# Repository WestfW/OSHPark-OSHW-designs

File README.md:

# OSHPark-OSHW-designs
I have some PCB projects that I've made public on OSHPark.  This is where I'll put the "source code" and any documentation that may exist.

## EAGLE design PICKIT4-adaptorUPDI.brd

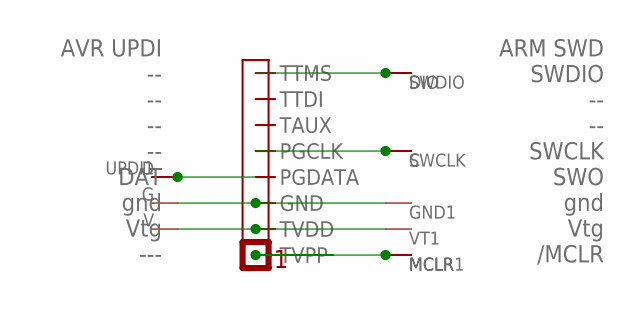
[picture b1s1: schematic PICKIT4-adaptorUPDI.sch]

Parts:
C: WIRER; GENERIC-RD-1
D: WIRER; GENERIC-RD-1
DIO: WIRER; GENERIC-RD-1
G: WIRER; GENERIC-RD-1
GND1: WIRE-R12; VIA12
MCLR: WIRE-R12; VIA12
MCLR1: WIRER; GENERIC-RD-1
SWCLK: WIRE-R12; VIA12
SWDIO: WIRE-R12; VIA12
U$1: PICKIT4PINHDR; PINHEAD1X8
UPDI1: WIRE-R12; VIA12
V: WIRER; GENERIC-RD-1
VT1: WIRE-R12; VIA12

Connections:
GND: G.P$1, GND1.P$1, U$1.P$3 (GND)
unnamed: U$1.P$2 (TVDD), V.P$1, VT1.P$1
unnamed: D.P$1, U$1.P$4 (PGDATA), UPDI1.P$1
unnamed: C.P$1, SWCLK.P$1, U$1.P$5 (PGCLK)
TTMS: DIO.P$1, SWDIO.P$1, U$1.P$8 (TTMS)
TVPP: MCLR.P$1, MCLR1.P$1, U$1.P$1 (TVPP)

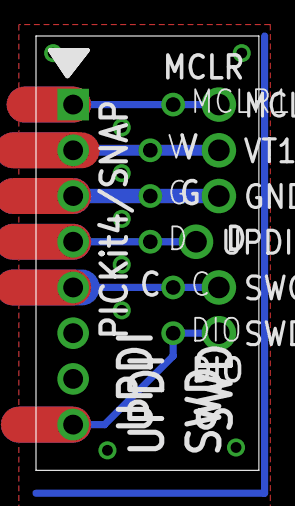
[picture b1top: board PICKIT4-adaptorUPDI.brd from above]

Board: 2 copper layers, 12.4 x 24.1 mm, 13 parts (0 on the bottom side), 6 nets.

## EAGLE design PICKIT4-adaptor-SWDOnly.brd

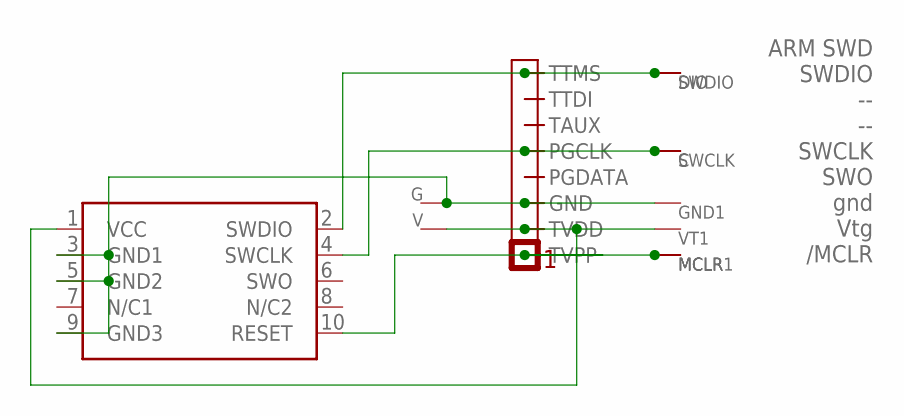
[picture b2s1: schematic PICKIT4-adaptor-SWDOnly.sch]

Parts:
C: WIRE-R12; VIA12
DIO: WIRE-R12; VIA12
G: WIRE-R12; VIA12
GND1: WIRE-R12; VIA12
MCLR, MCLR1: WIRE-R12; VIA12
SWCLK: WIRE-R12; VIA12
SWD1: CORTEX_SWD; M50-3600542
SWDIO: WIRE-R12; VIA12
U$1: PICKIT4PINHDR; PINHEAD1X8
V: WIRE-R12; VIA12
VT1: WIRE-R12; VIA12

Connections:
GND: G.P$1, GND1.P$1, SWD1.3 (GND1), SWD1.5 (GND2), SWD1.9 (GND3), U$1.P$3 (GND)
unnamed: SWD1.1 (VCC), U$1.P$2 (TVDD), V.P$1, VT1.P$1
unnamed: C.P$1, SWCLK.P$1, SWD1.4 (SWCLK), U$1.P$5 (PGCLK)
unnamed: MCLR.P$1, MCLR1.P$1, SWD1.10 (RESET), U$1.P$1 (TVPP)
TTMS: DIO.P$1, SWD1.2 (SWDIO), SWDIO.P$1, U$1.P$8 (TTMS)

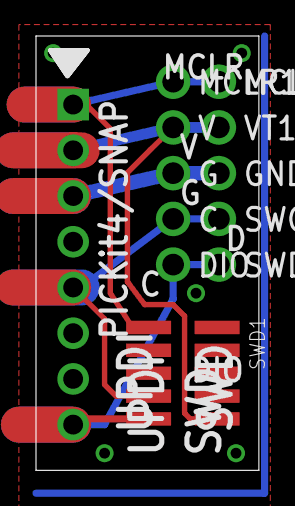
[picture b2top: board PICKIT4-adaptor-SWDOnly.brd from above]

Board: 2 copper layers, 12.4 x 24.1 mm, 12 parts (0 on the bottom side), 5 nets.

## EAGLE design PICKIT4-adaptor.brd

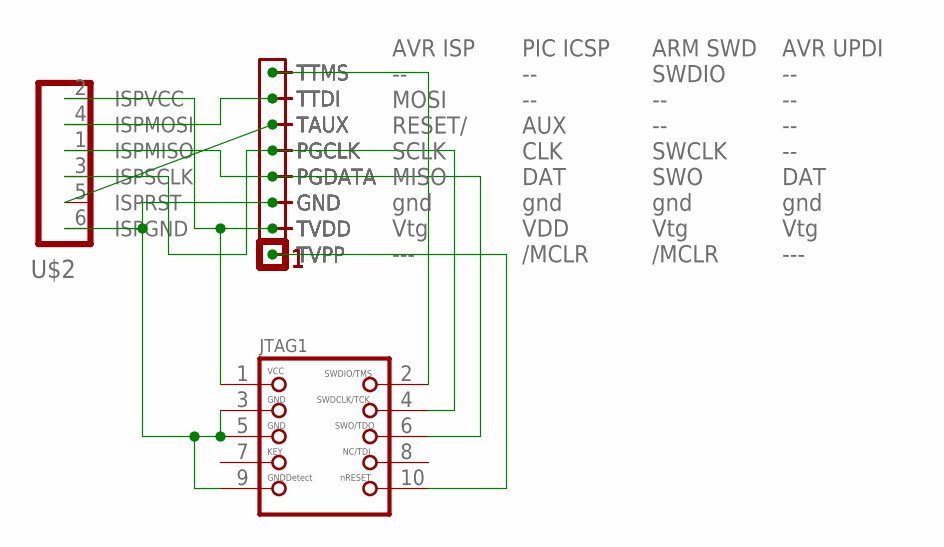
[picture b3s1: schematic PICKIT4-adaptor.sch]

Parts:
JTAG1: JTAG-CORTEXM3; 2X05_1.27MM_SMT
U$1, U$3, U$4: PICKIT4PINHDR; PINHEAD1X8
U$2: AVR-ISP; 6PINS

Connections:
CLK: JTAG1.4, U$1.P$5 (PGCLK), U$2.3 (ISPSCLK), U$3.P$5 (PGCLK), U$4.P$5 (PGCLK)
DATA: JTAG1.6, U$1.P$4 (PGDATA), U$2.1 (ISPMISO), U$3.P$4 (PGDATA), U$4.P$4 (PGDATA)
GND: JTAG1.3, JTAG1.5, JTAG1.9, U$1.P$3 (GND), U$2.6 (ISPGND), U$3.P$3 (GND), U$4.P$3 (GND)
TAUX: U$1.P$6 (TAUX), U$2.5 (ISPRST), U$3.P$6 (TAUX), U$4.P$6 (TAUX)
TTDI: U$1.P$7 (TTDI), U$2.4 (ISPMOSI), U$3.P$7 (TTDI), U$4.P$7 (TTDI)
TTMS: JTAG1.2, U$1.P$8 (TTMS), U$3.P$8 (TTMS), U$4.P$8 (TTMS)
TVDD: JTAG1.1, U$1.P$2 (TVDD), U$2.2 (ISPVCC), U$3.P$2 (TVDD), U$4.P$2 (TVDD)
VPP: JTAG1.10, U$1.P$1 (TVPP), U$3.P$1 (TVPP), U$4.P$1 (TVPP)

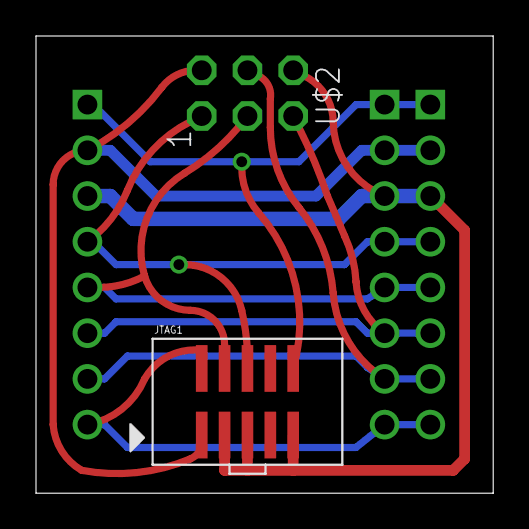
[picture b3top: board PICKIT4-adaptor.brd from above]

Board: 2 copper layers, 25.4 x 25.4 mm, 5 parts (0 on the bottom side), 8 nets.

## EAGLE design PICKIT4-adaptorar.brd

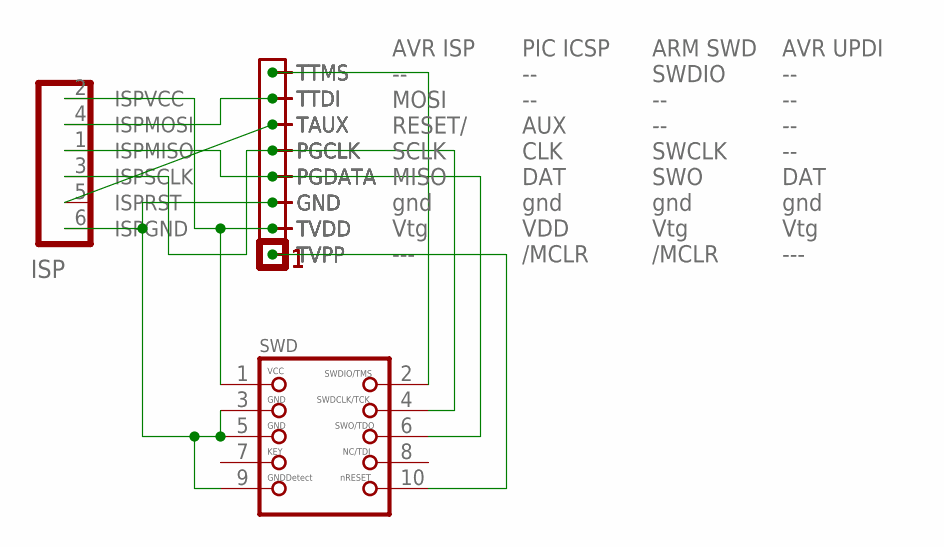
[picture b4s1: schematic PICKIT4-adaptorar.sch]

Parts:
ISP: AVR-ISP; 6PINS
SWD: JTAG-CORTEXM3; 2X05_1.27MM_SMT
U$1, U$3, U$4: PICKIT4PINHDR; PINHEAD1X8

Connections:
CLK: ISP.3 (ISPSCLK), SWD.4, U$1.P$5 (PGCLK), U$3.P$5 (PGCLK), U$4.P$5 (PGCLK)
DATA: ISP.1 (ISPMISO), SWD.6, U$1.P$4 (PGDATA), U$3.P$4 (PGDATA), U$4.P$4 (PGDATA)
GND: ISP.6 (ISPGND), SWD.3, SWD.5, SWD.9, U$1.P$3 (GND), U$3.P$3 (GND), U$4.P$3 (GND)
TAUX: ISP.5 (ISPRST), U$1.P$6 (TAUX), U$3.P$6 (TAUX), U$4.P$6 (TAUX)
TTDI: ISP.4 (ISPMOSI), U$1.P$7 (TTDI), U$3.P$7 (TTDI), U$4.P$7 (TTDI)
TTMS: SWD.2, U$1.P$8 (TTMS), U$3.P$8 (TTMS), U$4.P$8 (TTMS)
TVDD: ISP.2 (ISPVCC), SWD.1, U$1.P$2 (TVDD), U$3.P$2 (TVDD), U$4.P$2 (TVDD)
VPP: SWD.10, U$1.P$1 (TVPP), U$3.P$1 (TVPP), U$4.P$1 (TVPP)

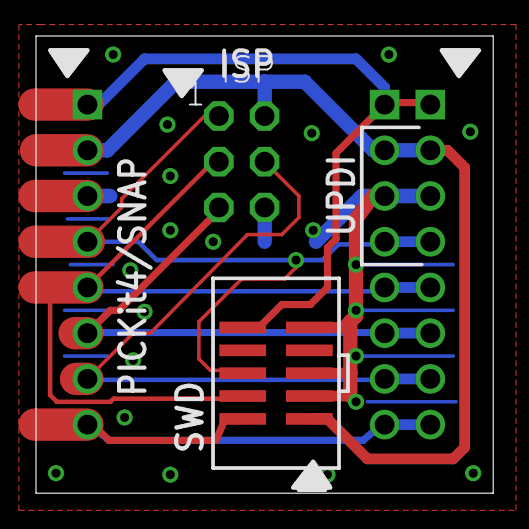
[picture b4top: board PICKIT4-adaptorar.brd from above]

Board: 2 copper layers, 25.4 x 25.4 mm, 5 parts (0 on the bottom side), 8 nets.

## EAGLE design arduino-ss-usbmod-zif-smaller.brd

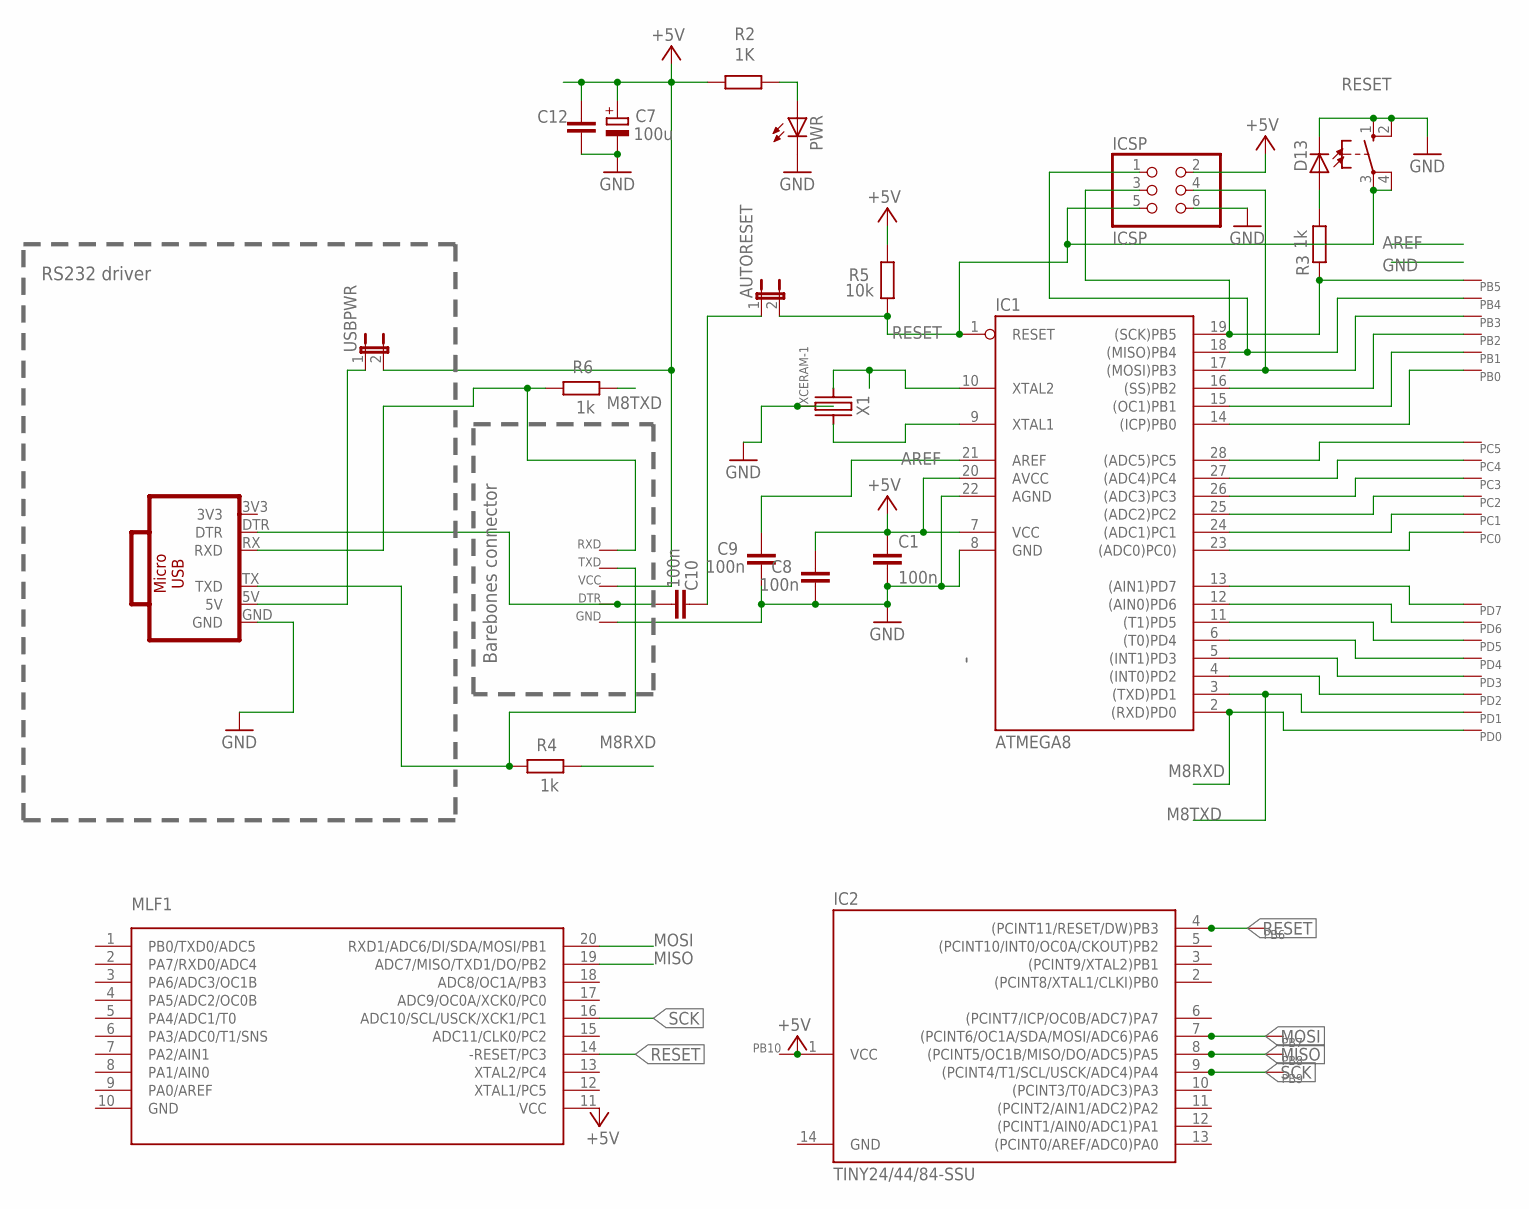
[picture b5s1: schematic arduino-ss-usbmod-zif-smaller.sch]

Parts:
AUTORESET: JUMPER-2PTH; 1X02
C1, C8, C9, C10, C12: 100n; C050-025X075
C7: 100u; E3,5-8
D13: LED3MM
DTR: WIRER; GENERIC-RD-1
GND: WIRER; GENERIC-RD-1
IC1: ATMEGA8; ZIF28/3
IC2: TINY24/44/84-SSU; SOIC14
ICSP: ICSP; 2X03
MLF1: ATTINY1634SOIC20; SOIC20
MOD1: CH340E-MODNOHOLES; CH340E-MOD-NOHOLES
PB0, PB1, PB2, PB3, PB4, PB5, PB6, PB7, PB8, PB9, PB10: WIRE-VIA11; VIA11
PC0: WIRER; GENERIC-RD-1
PC1, PC2, PC3, PC4, PC5: WIRE-VIA11; VIA11
PD0, PD1, PD2, PD3, PD4, PD5, PD6, PD7: WIRE-VIA11; VIA11
PWR: LED3MM
R2: 1K; 0207/7
R3: 1k; 0204/5
R4, R6: 1k; 0207/7
R5: 10k; 0207/7
RESET: 10-XX; B3F-10XX
RXD: WIRER; GENERIC-RD-1
TXD: WIRER; GENERIC-RD-1
USBPWR: JUMPER-2PTH; 1X02
VCC: WIRE-VIA11; VIA11
X1: XCERAM-1; XTAL-3

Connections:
3V3: MOD1.3V3
+5V: C1.1, C7.+, C8.2, C12.2, IC1.7 (VCC), IC1.20 (AVCC), IC2.1 (VCC), ICSP.2, MLF1.11 (VCC), PB10.P$1, R2.2, R5.2, USBPWR.2, VCC.P$1
AREF: C9.2, IC1.21 (AREF)
DTR: C10.1, DTR.P$1, MOD1.DTR
GND: C1.2, C7.-, C8.1, C9.1, C12.1, D13.K (C), GND.P$1, IC1.8 (GND), IC1.22 (AGND), IC2.14 (GND), ICSP.6, MLF1.10 (GND), MOD1.GND, PWR.K (C), RESET.1 (S), RESET.2 (S1), X1.P$2 (GND)
M8RXD: IC1.2 ((RXD)PD0), PD0.P$1, R4.1
M8TXD: IC1.3 ((TXD)PD1), PD1.P$1, R6.1
MISO: IC1.18 ((MISO)PB4), IC2.8 ((PCINT5/OC1B/MISO/DO/ADC5)PA5), ICSP.1, MLF1.19 (ADC7/MISO/TXD1/DO/PB2), PB4.P$1, PB8.P$1
MOSI: IC1.17 ((MOSI)PB3), IC2.7 ((PCINT6/OC1A/SDA/MOSI/ADC6)PA6), ICSP.4, MLF1.20 (RXD1/ADC6/DI/SDA/MOSI/PB1), PB3.P$1, PB7.P$1
unnamed: D13.A, R3.1
unnamed: MOD1.5V, USBPWR.1
unnamed: PWR.A, R2.1
unnamed: AUTORESET.1, C10.2
unnamed: IC1.14 ((ICP)PB0), PB0.P$1
unnamed: IC1.9 (XTAL1), X1.P$3
unnamed: IC1.10 (XTAL2), X1.P$1
unnamed: IC1.4 ((INT0)PD2), PD2.P$1
unnamed: IC1.5 ((INT1)PD3), PD3.P$1
unnamed: IC1.6 ((T0)PD4), PD4.P$1
unnamed: IC1.11 ((T1)PD5), PD5.P$1
unnamed: IC1.12 ((AIN0)PD6), PD6.P$1
unnamed: IC1.13 ((AIN1)PD7), PD7.P$1
unnamed: IC1.23 ((ADC0)PC0)), PC0.P$1
unnamed: IC1.24 ((ADC1)PC1), PC1.P$1
unnamed: IC1.25 ((ADC2)PC2), PC2.P$1
unnamed: IC1.26 ((ADC3)PC3), PC3.P$1
unnamed: IC1.27 ((ADC4)PC4), PC4.P$1
unnamed: IC1.28 ((ADC5)PC5), PC5.P$1
unnamed: IC1.15 ((OC1)PB1), PB1.P$1
unnamed: MOD1.TX (TXD), R4.2, TXD.P$1
unnamed: MOD1.RX (RXD), R6.2, RXD.P$1
RESET: AUTORESET.2, IC1.1 (RESET), IC2.4 ((PCINT11/RESET/DW)PB3), ICSP.5, MLF1.14 (-RESET/PC3), PB6.P$1, R5.1, RESET.3, RESET.4 (P1)
SCK: IC1.19 ((SCK)PB5), IC2.9 ((PCINT4/T1/SCL/USCK/ADC4)PA4), ICSP.3, MLF1.16 (ADC10/SCL/USCK/XCK1/PC1), PB5.P$1, PB9.P$1, R3.2
SS: IC1.16 ((SS)PB2), PB2.P$1

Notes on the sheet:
RS232 driver
Barebones connector

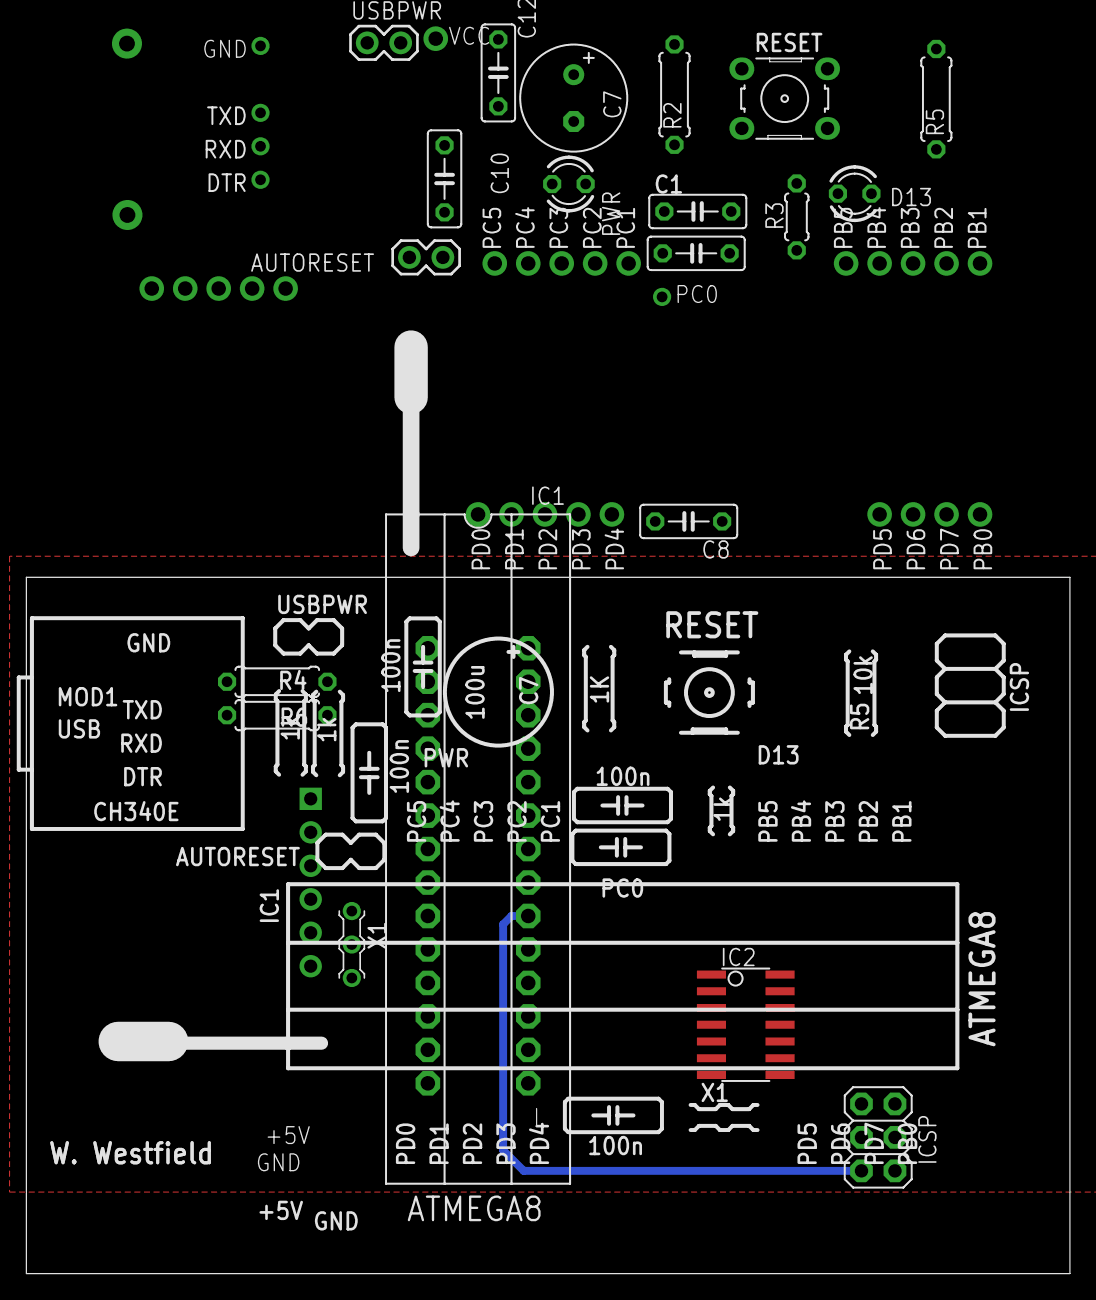
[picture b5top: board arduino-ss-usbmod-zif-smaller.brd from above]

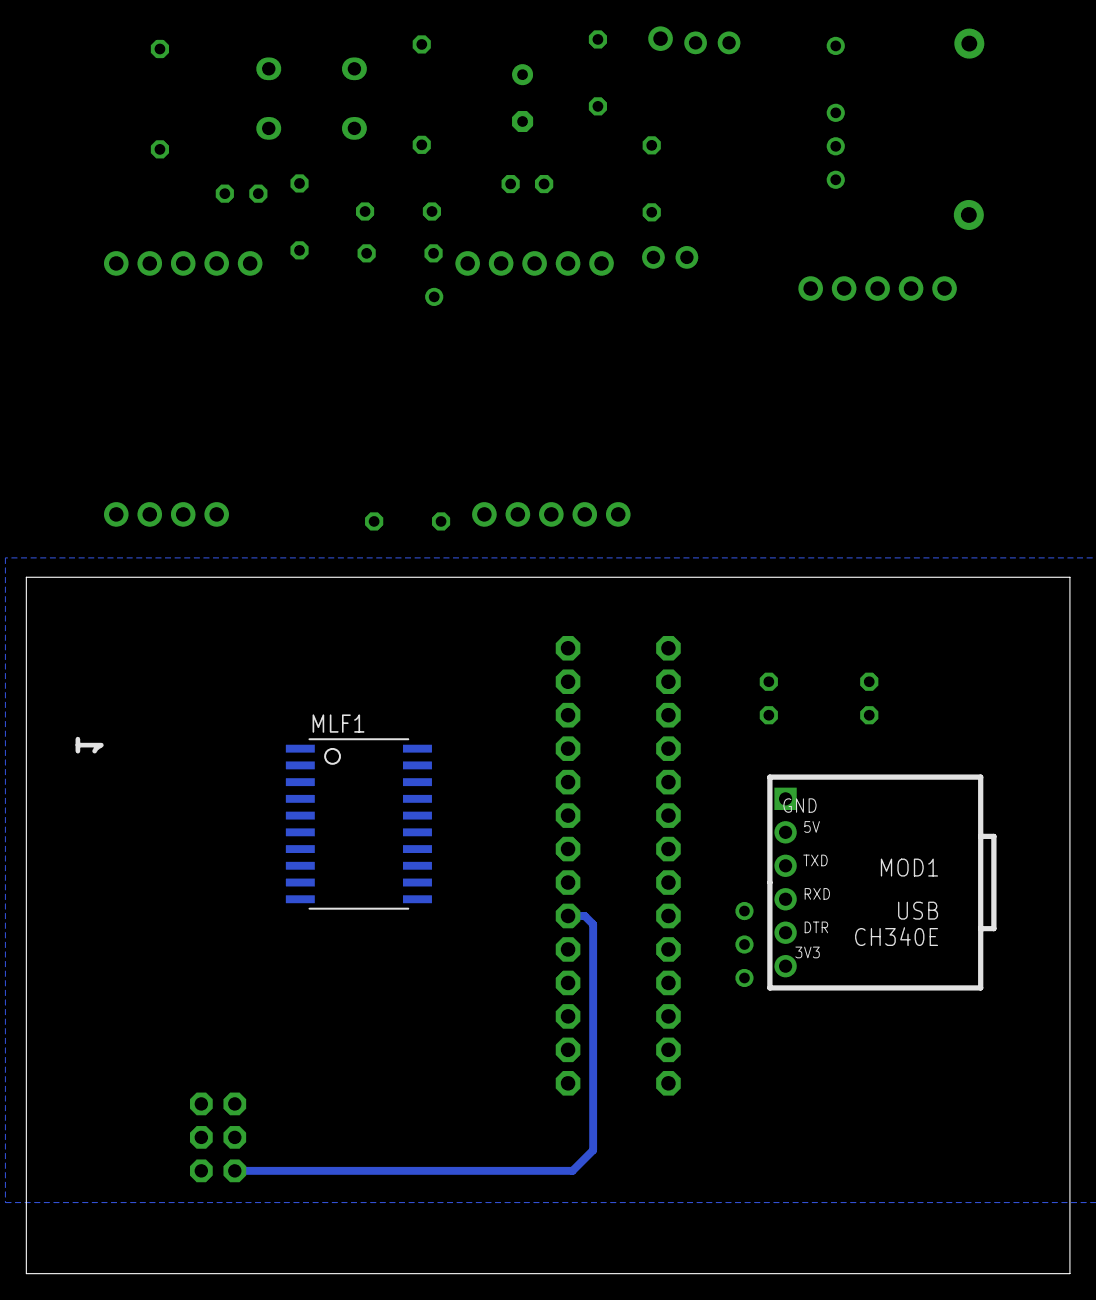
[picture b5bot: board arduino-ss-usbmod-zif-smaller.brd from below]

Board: 2 copper layers, 79.2 x 52.9 mm, 52 parts (2 on the bottom side), 33 nets.

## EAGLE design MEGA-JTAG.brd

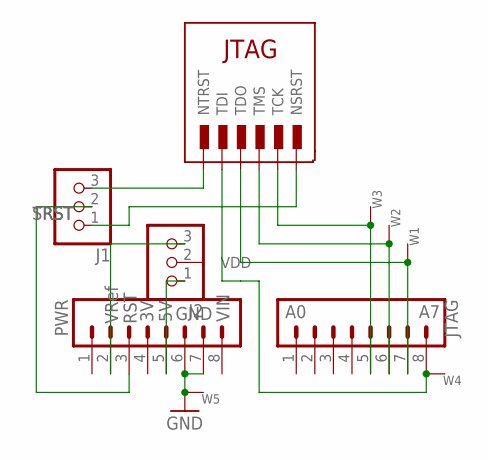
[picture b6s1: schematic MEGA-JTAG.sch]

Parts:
J1, J2: JUMPER_1X3ALT; JUMPER_SOLDER
JP1: JTAG; 1X08_LOCK_LONGPADS
JP2: PWR; 1X08_LOCK_LONGPADS
U$1: JTAG6/10; JTAG10
W1, W2, W3, W4, W5: WIRE-VIA8; VIA8

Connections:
GND: JP2.6, JP2.7, U$1.2.GND (GND), U$1.10.GND (GND), W5.P$1
unnamed: J1.3, U$1.8.NTRST (NTRST)
unnamed: J1.1, U$1.6.NSRST (NSRST)
unnamed: J2.2, U$1.4.VTREF (VDD)
unnamed: J2.1, JP2.5
unnamed: J2.3, JP2.2
NSRST: J1.2, JP2.3
TCK: JP1.5, U$1.1.TCK (TCK), W3.P$1
TDI: JP1.8, U$1.9.TDI (TDI), W4.P$1
TDO: JP1.7, U$1.3.TDO (TDO), W1.P$1
TMS: JP1.6, U$1.5.TMS (TMS), W2.P$1

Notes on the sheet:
VIN
GND
RST
VRef

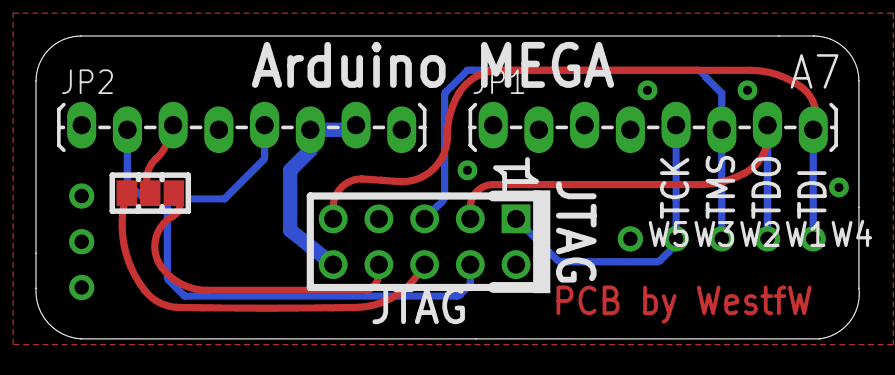
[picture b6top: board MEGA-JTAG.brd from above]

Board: 2 copper layers, 45.7 x 16.8 mm, 10 parts (1 on the bottom side), 11 nets.

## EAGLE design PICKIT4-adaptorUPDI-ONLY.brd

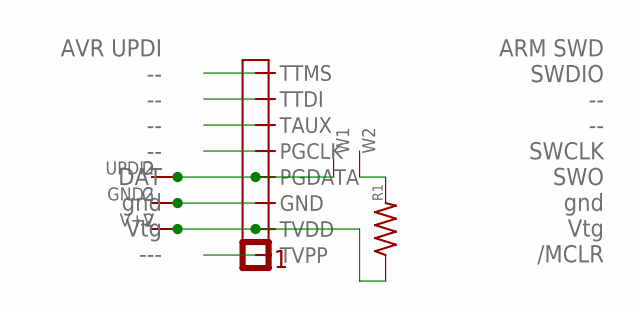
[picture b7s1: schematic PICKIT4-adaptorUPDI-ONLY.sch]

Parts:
D: WIRE-R10; VIA10
G: WIRE-R10; VIA10
GND2: WIRE-R12; VIA12
R1: R-US_0204/7; 0204/7
U$1: PICKIT4PINHDR; PINHEAD1X8
UPDI2: WIRE-R12; VIA12
V: WIRE-R10; VIA10
V+2: WIRE-R12; VIA12
W1, W2: WIRE-R10; VIA10

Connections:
GND: G.P$1, GND2.P$1, U$1.P$3 (GND)
unnamed: R1.1, U$1.P$2 (TVDD), V.P$1, V+2.P$1
unnamed: D.P$1, U$1.P$4 (PGDATA), UPDI2.P$1, W1.P$1
unnamed: R1.2, W2.P$1

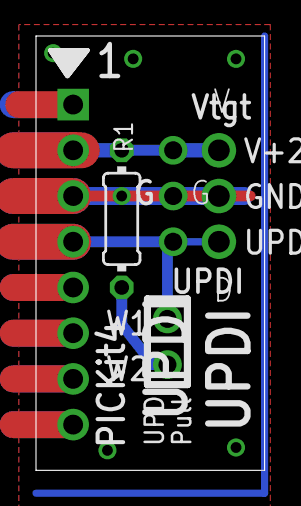
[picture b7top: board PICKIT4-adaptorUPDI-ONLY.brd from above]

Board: 2 copper layers, 12.7 x 24.1 mm, 10 parts (0 on the bottom side), 4 nets.

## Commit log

2020-09-19 Initial Commit some files

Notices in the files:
parts and their libraries:
SparkFun-Connectors: Licensing: CC v3.0 Share-Alike You are welcome to use this library for commercial purposes.
